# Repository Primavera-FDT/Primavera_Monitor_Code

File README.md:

# Primavera_Monitor_Code
Hello, this is the Source Code Repository for Primavera Monitor Project
## Website
The website where you can find the whole Primavera project is [Primavera-Project](https://primavera-project.com/)

-
-
-
-
-
-

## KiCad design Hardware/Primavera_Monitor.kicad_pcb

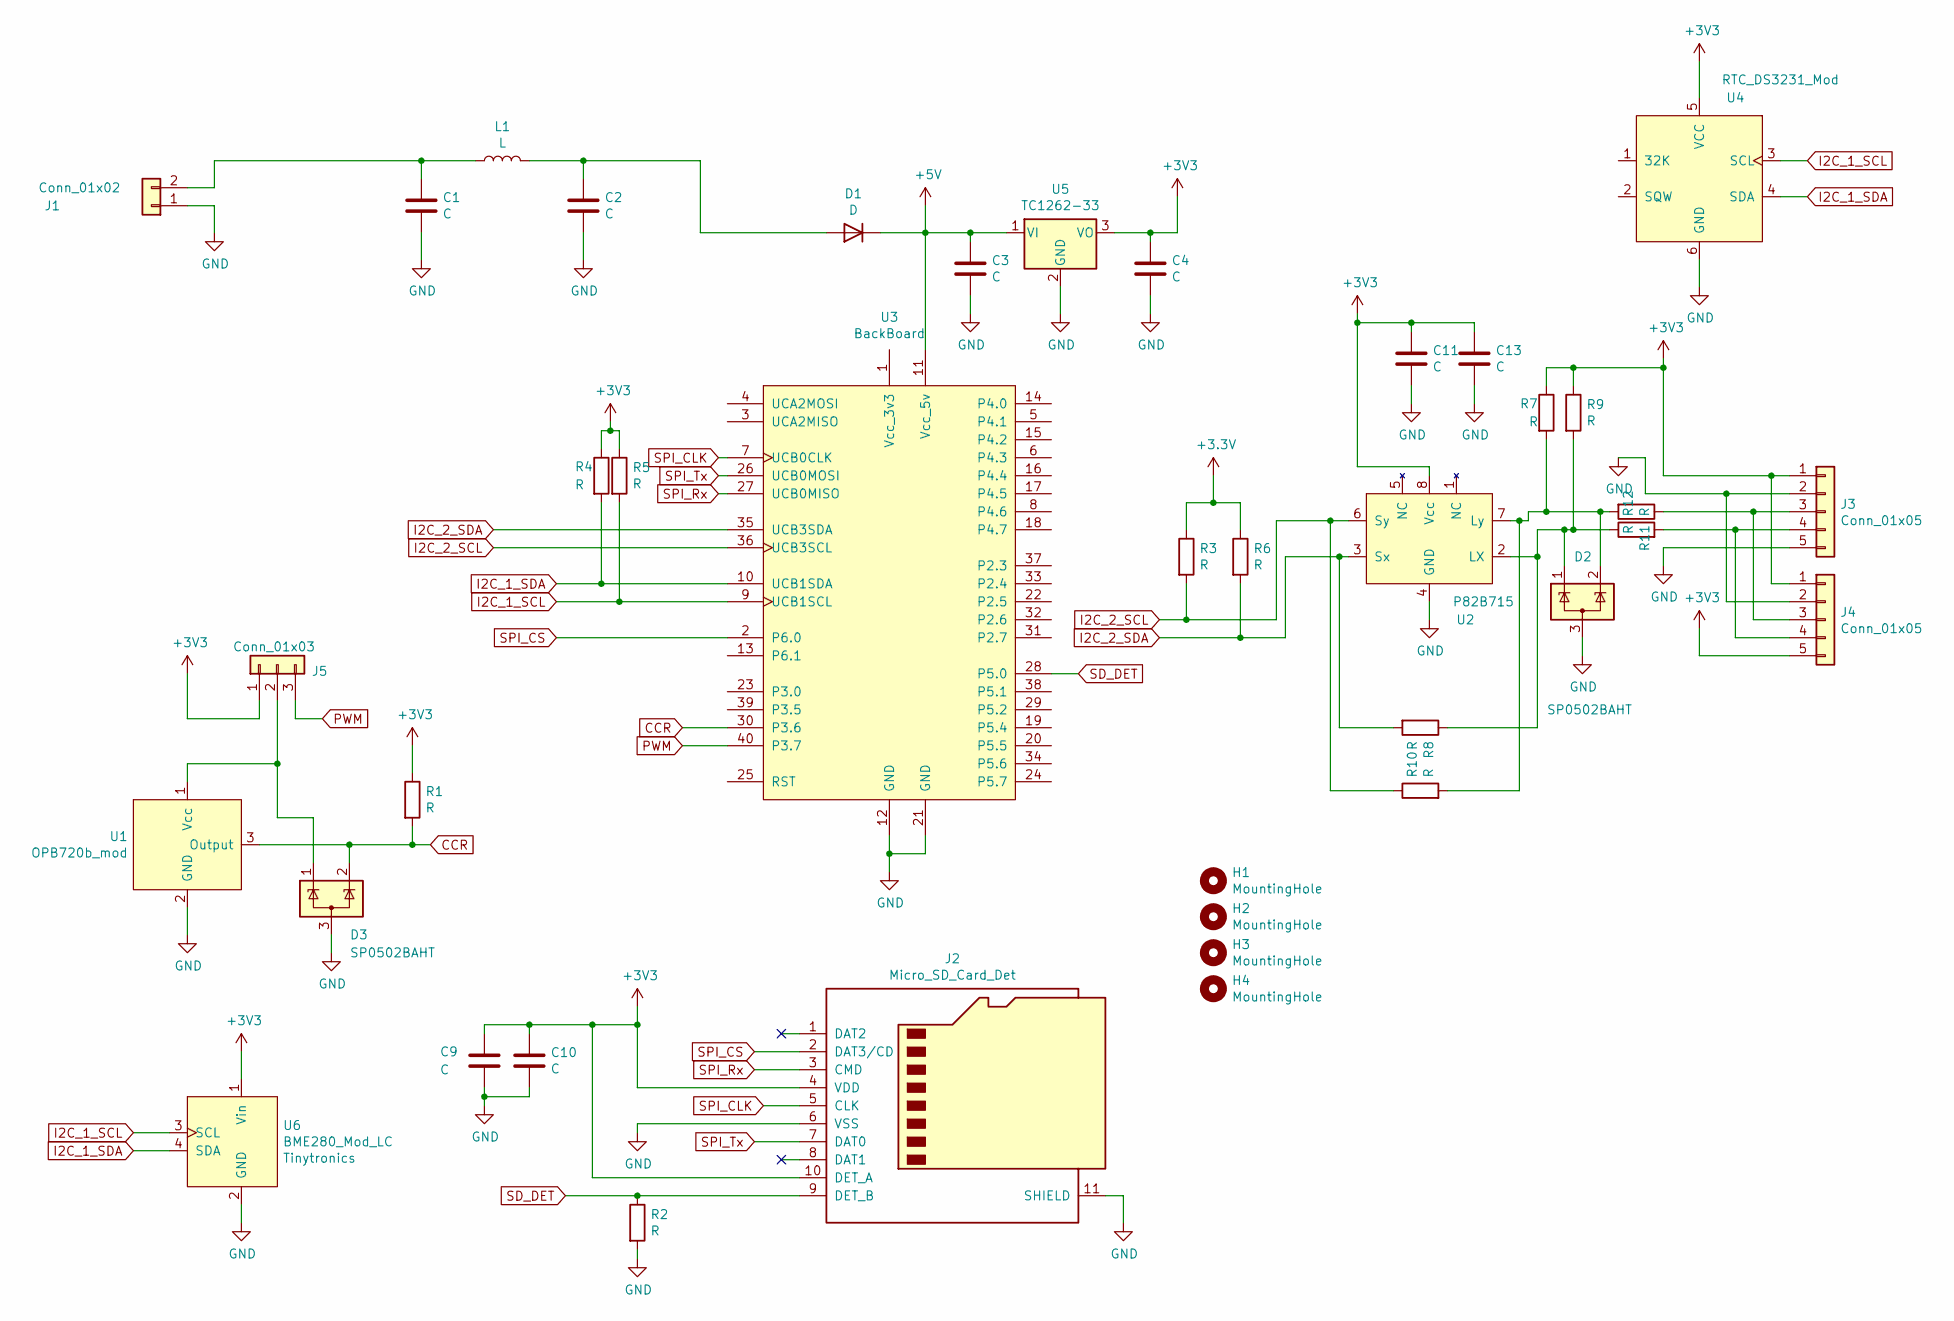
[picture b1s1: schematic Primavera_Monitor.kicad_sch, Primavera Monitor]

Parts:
C1, C2: C; C_1210_3225Metric
C3, C4, C9, C10, C11, C13: C; C_0603_1608Metric_Pad1.08x0.95mm_HandSolder
D1: D; D_1206_3216Metric
D2, D3: SP0502BAHT; SOT-23
H1, H2, H3, H4: MountingHole; MountingHole_4mm
J1: Conn_01x02; Molex_KK-254_AE-6410-02A_1x02_P2.54mm_Vertical
J2: Micro_SD_Card_Det; microSD_HC_Hirose_DM3BT-DSF-PEJS
J3, J4: Conn_01x05; Molex_KK-254_AE-6410-05A_1x05_P2.54mm_Vertical
J5: Conn_01x03; PinHeader_1x03_P2.54mm_Vertical
L1: L; L_1210_3225Metric
R1, R2, R3, R4, R5, R6, R7, R8, R9, R10, R11, R12: R; R_0603_1608Metric_Pad0.98x0.95mm_HandSolder
U1: OPB720b_mod; Molex_KK-254_AE-6410-03A_1x03_P2.54mm_Vertical
U2: P82B715; SO-8_3.9x4.9mm_P1.27mm
U3: BackBoard; MSP-EXP432P401R-Backboard
U4: RTC_DS3231_Mod; PinSocket_1x06_P2.54mm_Vertical
U5: TC1262-33; SOT-223-3_TabPin2
U6: BME280_Mod_LC; PinSocket_1x06_P2.54mm_Horizontal

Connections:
+5V: C3.1, D1.1 (K), U3.11 (Vcc_5v), U5.1 (VI)
CCR: D3.2 (K), R1.2, U1.3 (Output), U3.30 (P3.6)
GND: C1.2, C2.2, C3.2, C4.2, C9.1, C10.2, C11.2, C13.2, D2.3 (A), D3.3 (A), J1.1, J2.6 (VSS), J2.11 (SHIELD), J3.2, J3.5, J4.2, R2.2, U1.2 (GND), U2.4 (GND), U3.12 (GND), U3.21 (GND), U4.6 (GND), U5.2 (GND), U6.2 (GND)
I2C_1_SCL: R5.2, U3.9 (UCB1SCL), U4.3 (SCL), U6.3 (SCL)
I2C_1_SDA: R4.2, U3.10 (UCB1SDA), U4.4 (SDA), U6.4 (SDA)
I2C_2_SCL: R3.2, R10.1, U2.6 (Sy), U3.36 (UCB3SCL)
I2C_2_SDA: R6.2, R8.2, U2.3 (Sx), U3.35 (UCB3SDA)
unnamed: C1.1, J1.2, L1.1
unnamed: C2.1, D1.2 (A), L1.2
unnamed: D2.1 (K), R8.1, R9.2, R12.1, U2.2 (LX)
unnamed: D2.2 (K), R7.2, R10.2, R11.2, U2.7 (Ly)
unnamed: D3.1 (K), J5.2, U1.1 (Vcc)
unnamed: J3.3, J4.3, R11.1
unnamed: J3.4, J4.4, R12.2
PWM: J5.3, U3.40 (P3.7)
SD_DET: J2.9 (DET_B), R2.1, U3.28 (P5.0)
SPI_CLK: J2.5 (CLK), U3.7 (UCB0CLK)
SPI_CS: J2.2 (DAT3/CD), U3.2 (P6.0)
SPI_Rx: J2.3 (CMD), U3.27 (UCB0MISO)
SPI_Tx: J2.7 (DAT0), U3.26 (UCB0MOSI)

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
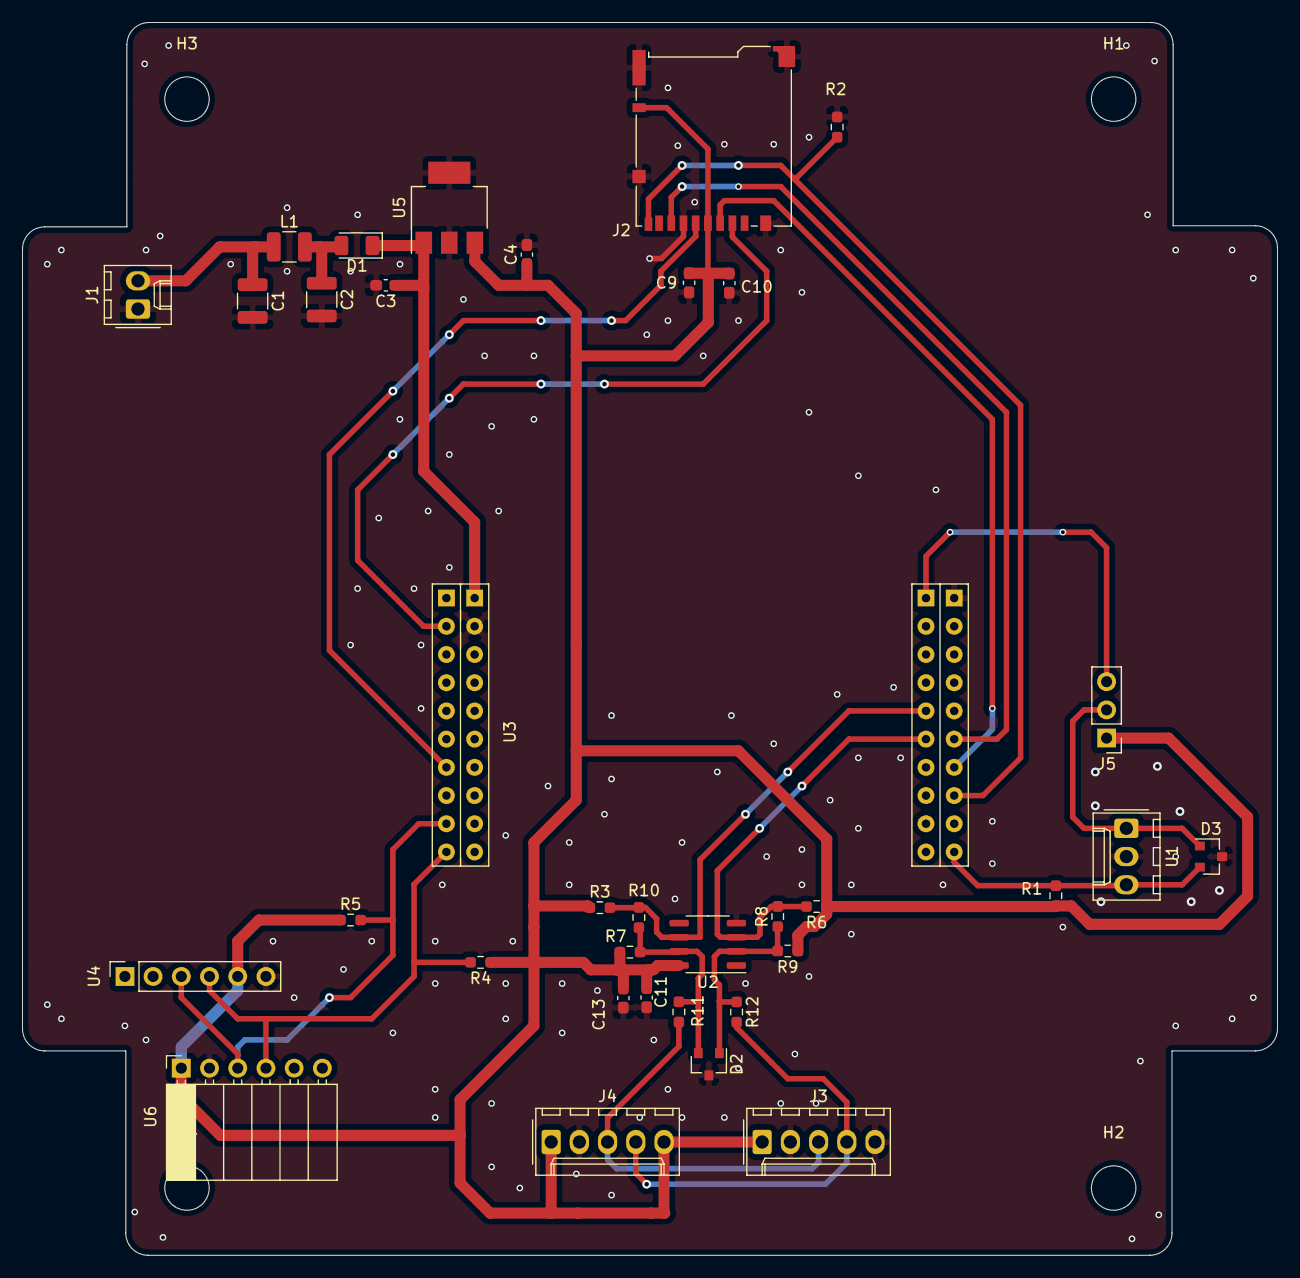
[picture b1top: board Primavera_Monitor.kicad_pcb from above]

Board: 2 copper layers, 113.0 x 111.0 mm, 39 parts (0 on the bottom side), 21 nets.

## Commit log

2021-09-01 Add README.txt
2021-09-08 new README
2021-09-08 making changes
2021-09-08 adding .gitignore file
2021-09-23 Update README.md
    Adding the website of the project to the README
2021-09-30 Add kicad ignore files
2021-09-30 Add filters to make diffing more usefull
2021-09-30 Add sym-lib-table to ignore
2021-09-30 Add symbols for BME280 and its modules
    This commit adds the following the following symbols to the
    BME280 library:
    1. BME280
    2. BME280 Module with level converter
    3. BME280 Module
2021-09-30 Ignore fp-lib-table
2021-09-30 Add footprint association for BME280
2021-09-30 Adding the library of the MPU6050 module
2021-09-30 Adding the footprint asociated with the mpu6050 component
2021-09-30 Adding the new schematics and footprints of E18-D80NK and OPB720b, issues #5 and #6
2021-10-01 adding the RTC schematic and footprint, issue #7
2021-10-06 adding changes int some schematic components and deleting the footprints that are not neccesary
2021-10-06 Adding the schematic symbol of the dc-dc converter LM2596
2021-10-07 Add initial revision
2021-10-30 Add *-rescue* files to ignore list
2021-10-30 Add Pi filter and diode switch to power supply
2021-10-30 add footprint to symbol
2021-10-30 Load improved msp-exp symbol
2021-10-30 Add pin information to symbol
2021-10-30 Add new SD Card Interface symbol to sch
2021-11-20 Add basic template for firmware
2021-11-23 Make the Makefile compatible between environments
2021-11-24 Add Long I2C module
2021-11-24 Add EMC protection, Long I2C and sd card on pcb
2021-11-26 adding the filesdataconv.c and dataconv.h, which are the files or hte convertion of numerical data into strings
2021-11-29 Add PCB design
2021-12-03 Change from last meeting
2021-12-12 Final Revision
2022-01-11 Add global array
2022-01-15 Added controllers
2022-01-15 Adding the headers and the .c files of the uart send a receive tasks, the streamer tasks and the uncomplete bem sensor tasks, also some changes made in the dataconv.c and dataconv.h files
2022-01-15 Changed comm mechanisms
2022-01-15 Improvements to header file
2022-01-15 adding the files of the sensor bme280 (bme.h and bme.c), and correcting errors in the file stream.c and dataconv.h
2022-01-15 Updates to the i2c
2022-01-27 update to software
2022-01-27 Up to date
2022-01-27 Modified
